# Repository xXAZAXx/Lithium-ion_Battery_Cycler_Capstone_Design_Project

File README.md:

# Lithium-ion_Battery_Cycler_Capstone_Design_Project
Designed and developed a low-cost automated single-cell lithium-ion battery cycler for controlled charge and discharge testing. The system integrates a custom PCB, microcontroller-based control, and real-time data acquisition using Python and MATLAB for visualization and analysis.

### Assembled PCB Hardware
The completed, soldered PCB used for the battery cycler system.

---

### PCB Schematic & 3D Render (KiCad)
Schematic and 3D render showing component placement and overall hardware design.

---

### MATLAB Standalone Application 
Custom MATLAB App Designer interface used for real-time visualization and analysis of charge/discharge data.

---

## Technologies Used
- **Embedded Systems:** Arduino / Microcontroller-based control  
- **Programming:** Python, MATLAB  
- **Hardware Design:** KiCad (PCB Design & Layout)  
- **Data Processing:** CSV logging, real-time plotting (Matplotlib / MATLAB)  

---

## Results
The system enables reliable and repeatable charge/discharge testing of lithium-ion cells, with real-time monitoring and post-processing for performance evaluation.

---

## Note
This project was developed as part of a fourth-year capstone design project at the University of Windsor.

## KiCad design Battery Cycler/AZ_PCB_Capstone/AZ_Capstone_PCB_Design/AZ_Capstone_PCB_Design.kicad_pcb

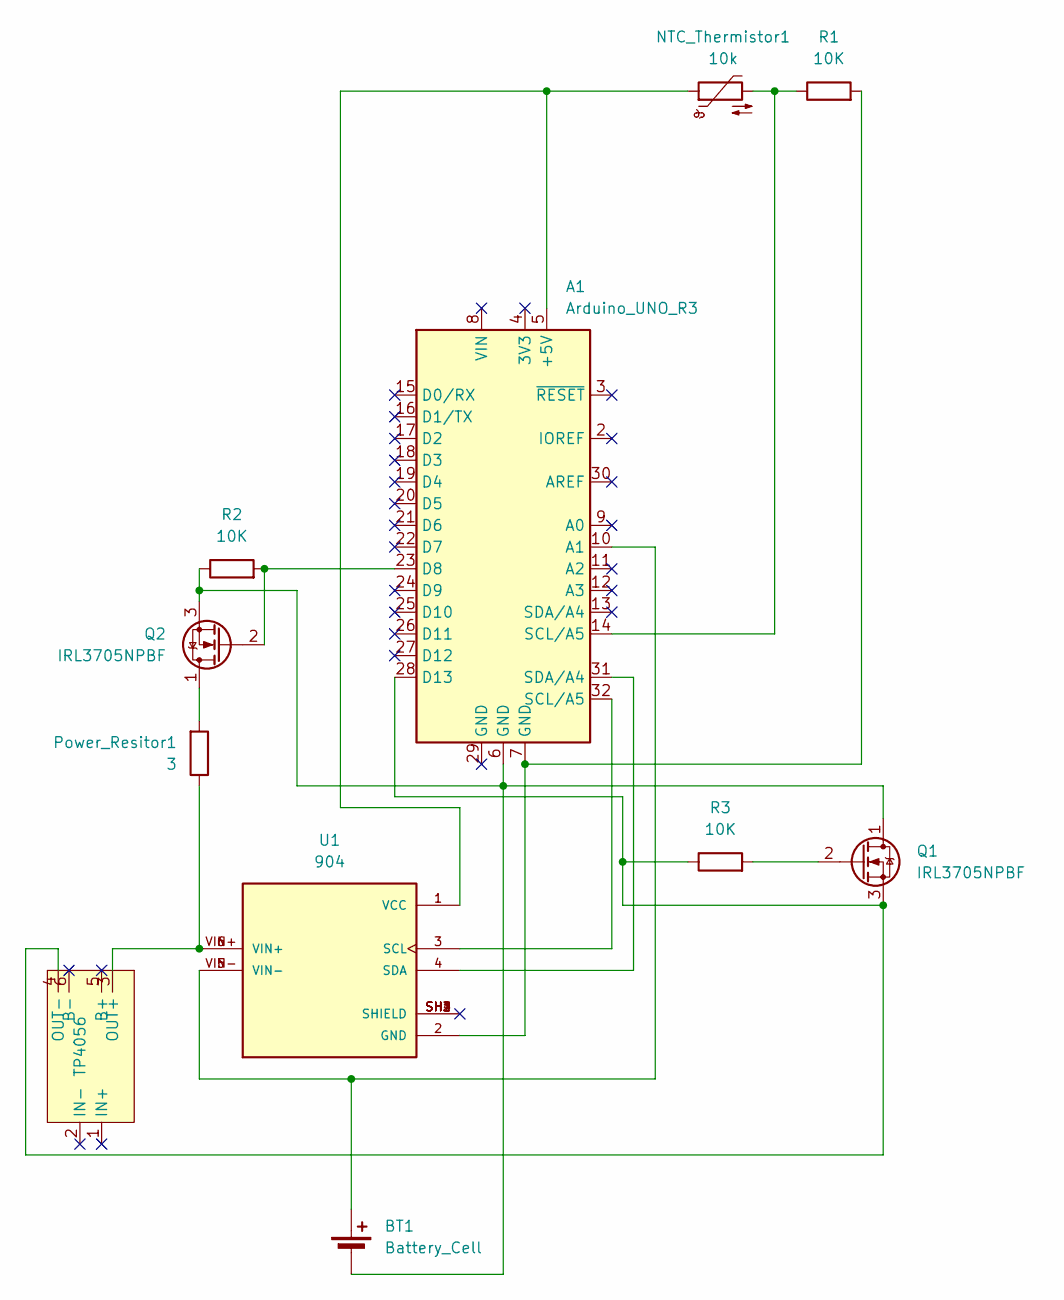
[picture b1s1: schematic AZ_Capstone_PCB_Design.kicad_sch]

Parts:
A1: Arduino_UNO_R3
BT1: Battery_Cell; 103048 Li-ion Polymer Battery
NTC_Thermistor1: 10k; R_0201_0603Metric_Pad0.64x0.40mm_HandSolder; Part No. MF51E103F3950
Power_Resitor1: 3; RES_20_OHM; Part No. 20J3R0E-ND
Q1, Q2: IRL3705NPBF; TO254P1041X444X1930-3; Part No. IRL3705NPBF
R1, R2, R3: 10K; R_Axial_DIN0207_L6.3mm_D2.5mm_P7.62mm_Horizontal
TP4056: TP4056-MODULE-AZ
U1: 904; MODULE_904; PARTREV C

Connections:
unnamed 0: A1.5 (+5V), NTC_Thermistor1.1, U1.1 (VCC); also elsewhere on the board
unnamed 1: A1.10 (A1), BT1.1 (+), U1.5 (VIN-), U1.VIN-; also elsewhere on the board
unnamed: A1.23 (D8), Q2.2 (G), R2.2
unnamed: A1.28 (D13), Q1.3 (S), R3.1, TP4056.4 (OUT-)
unnamed: A1.14 (SCL/A5), NTC_Thermistor1.2, R1.1
unnamed: A1.6 (GND), BT1.2 (-), Q1.1 (D), Q2.3 (S), R2.1
unnamed: Q1.2 (G), R3.2
unnamed: Power_Resitor1.2, Q2.1 (D)
unnamed 8: Power_Resitor1.1, TP4056.3 (OUT+), U1.6 (VIN+), U1.VIN+; also elsewhere on the board
unnamed 9: A1.7 (GND), R1.2, U1.2 (GND); also elsewhere on the board
unnamed: U1.SH1 (SHIELD), U1.SH2 (SHIELD), U1.SH3 (SHIELD), U1.SH4 (SHIELD)
unnamed 11: A1.32 (SCL/A5), U1.3 (SCL); also elsewhere on the board
unnamed 12: A1.31 (SDA/A4), U1.4 (SDA); also elsewhere on the board

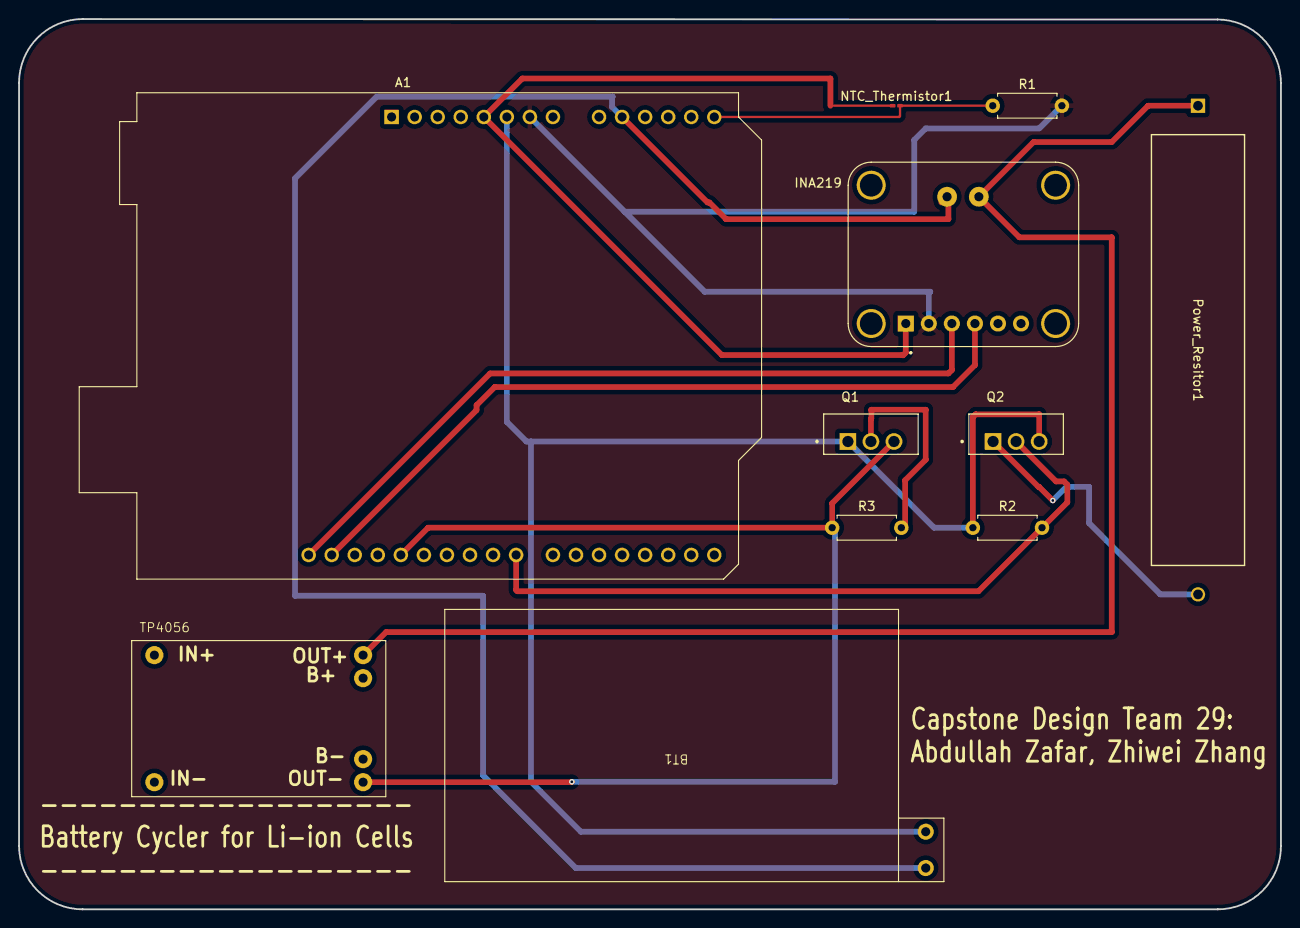
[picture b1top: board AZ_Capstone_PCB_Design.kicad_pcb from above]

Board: 2 copper layers, 139.1 x 98.1 mm, 11 parts (0 on the bottom side), 13 nets.

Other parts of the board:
INA219: 904; MODULE_904

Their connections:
unnamed 0: INA219.1 (VCC); also elsewhere on the board
unnamed 1: INA219.5 (VIN-), INA219.VIN-; also elsewhere on the board
unnamed 8: INA219.6 (VIN+), INA219.VIN+; also elsewhere on the board
unnamed 9: INA219.2 (GND); also elsewhere on the board
unnamed 11: INA219.3 (SCL); also elsewhere on the board
unnamed 12: INA219.4 (SDA); also elsewhere on the board
unnamed: INA219.SH1 (SHIELD), INA219.SH2 (SHIELD), INA219.SH3 (SHIELD), INA219.SH4 (SHIELD)
